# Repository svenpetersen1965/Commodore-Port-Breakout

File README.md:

# Commodore-Port-Breakout
There are five diffenet PCBs.
* 2x12 Breakout: A board that connects to the user port and the IEEE-488 port of the PET
* Cassette Breakout: A board that connects to the Cassette Port of the PET (and C64, C128 and VIC-20)
* Cassette Output: It contains a cassette port board edge connector and connects via a 6p ribbon cable to the Cassette Breakout board.
* IEEE-488 Output: It contains an IEEE-488  port board edge connector and connects via a 26p ribbon cable to the 2x12 Breakout board.
* User Port Output: It contains an User Port port board edge connector and connects via a 26p ribbon cable to the 2x12 Breakout board. It works as well with the C64, C128 and VIC-20

2x12 Breakout:<br>

Cassette Breakout:<br>

Cassette Output:<br>

IEEE-488 Output:<br>

User Port Output:<br>

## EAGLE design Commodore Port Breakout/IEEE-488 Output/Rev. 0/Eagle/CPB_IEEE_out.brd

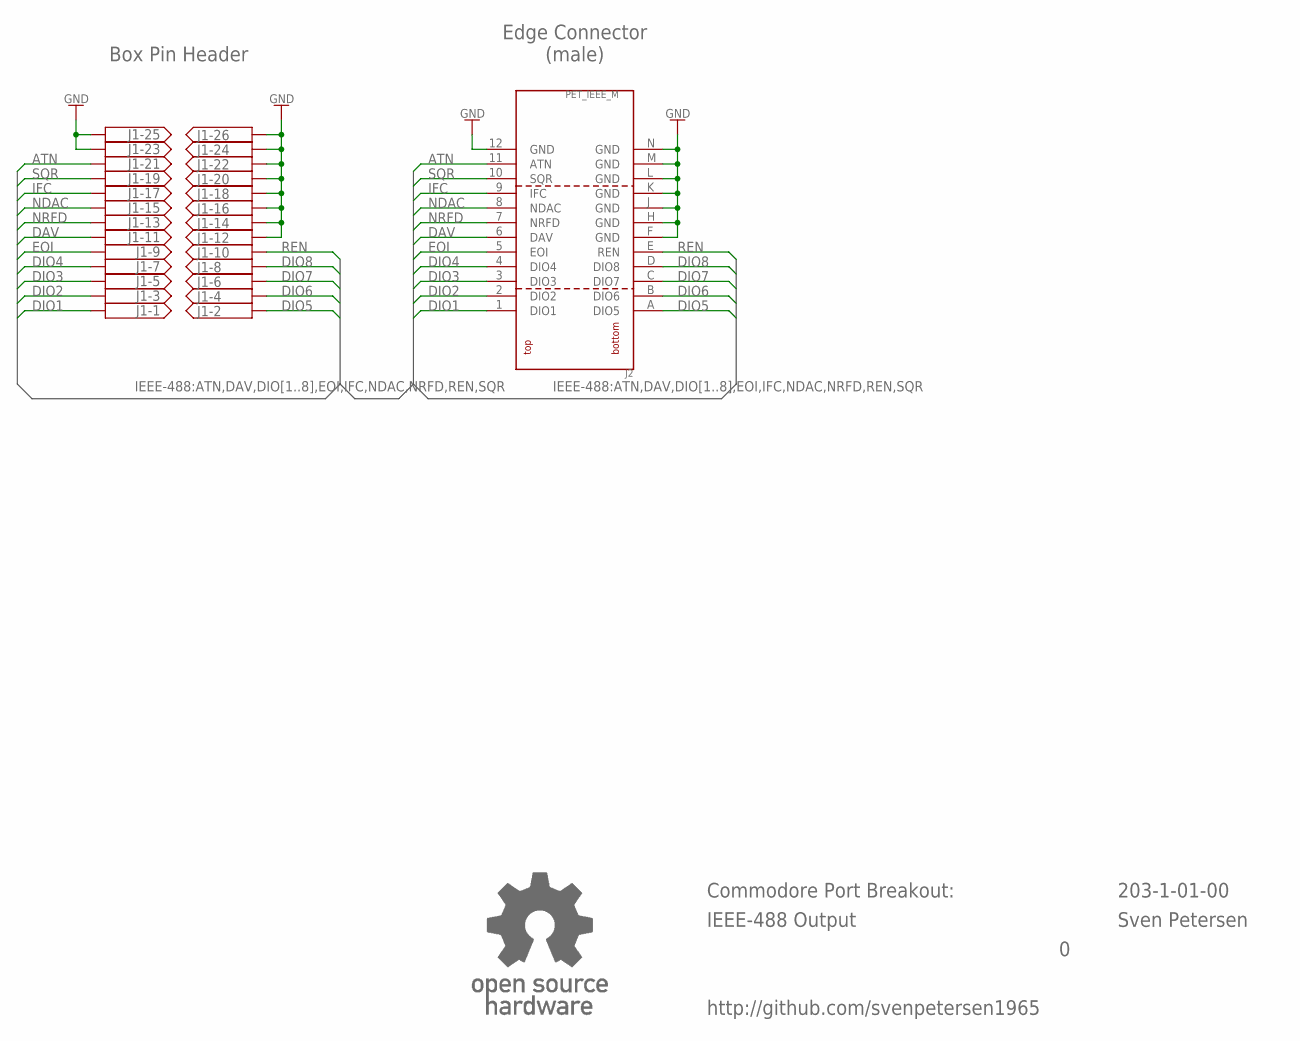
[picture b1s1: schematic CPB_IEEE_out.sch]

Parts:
J1: 2X13WANNE; 2X13WV
J2: PET_IEEE_M
U$9: OPEN_SOURCE_HW; OPENHW

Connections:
ATN: J1.21, J2.11 (ATN)
DAV: J1.11, J2.6 (DAV)
DIO1: J1.1, J2.1 (DIO1)
DIO2: J1.3, J2.2 (DIO2)
DIO3: J1.5, J2.3 (DIO3)
DIO4: J1.7, J2.4 (DIO4)
DIO5: J1.2, J2.A (DIO5)
DIO6: J1.4, J2.B (DIO6)
DIO7: J1.6, J2.C (DIO7)
DIO8: J1.8, J2.D (DIO8)
EOI: J1.9, J2.5 (EOI)
GND: J1.12, J1.14, J1.16, J1.18, J1.20, J1.22, J1.23, J1.24, J1.25, J1.26, J2.12 (GND), J2.F (GND), J2.H (GND), J2.J (GND), J2.K (GND), J2.L (GND), J2.M (GND), J2.N (GND)
IFC: J1.17, J2.9 (IFC)
NDAC: J1.15, J2.8 (NDAC)
NRFD: J1.13, J2.7 (NRFD)
REN: J1.10, J2.E (REN)
SQR: J1.19, J2.10 (SQR)

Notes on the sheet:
Commodore Port Breakout:
203-1-01-00
Sven Petersen
http://github.com/svenpetersen1965
IEEE-488 Output
Edge Connector (male)
Box Pin Header

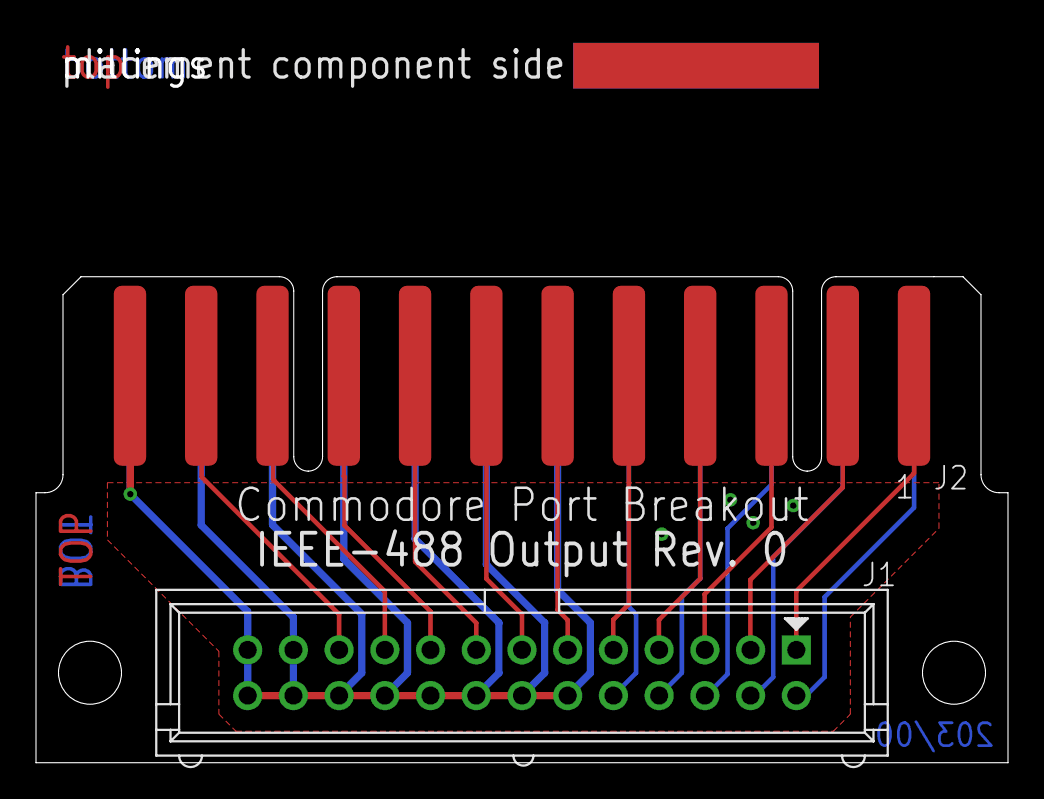
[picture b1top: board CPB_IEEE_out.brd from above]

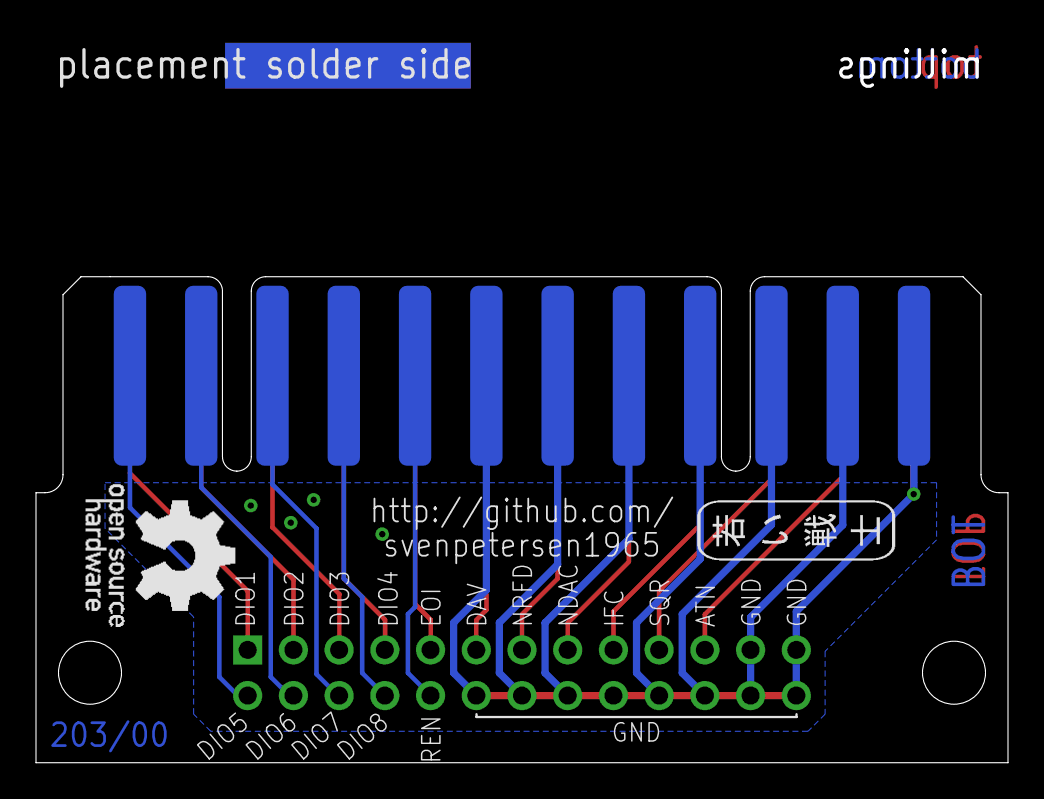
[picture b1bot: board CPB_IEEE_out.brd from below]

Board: 2 copper layers, 54.0 x 40.4 mm, 6 parts (2 on the bottom side), 17 nets.

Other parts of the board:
U$8: PCB-TITLE/
U$10: 2LAYER
U$11: SVEN_TAG

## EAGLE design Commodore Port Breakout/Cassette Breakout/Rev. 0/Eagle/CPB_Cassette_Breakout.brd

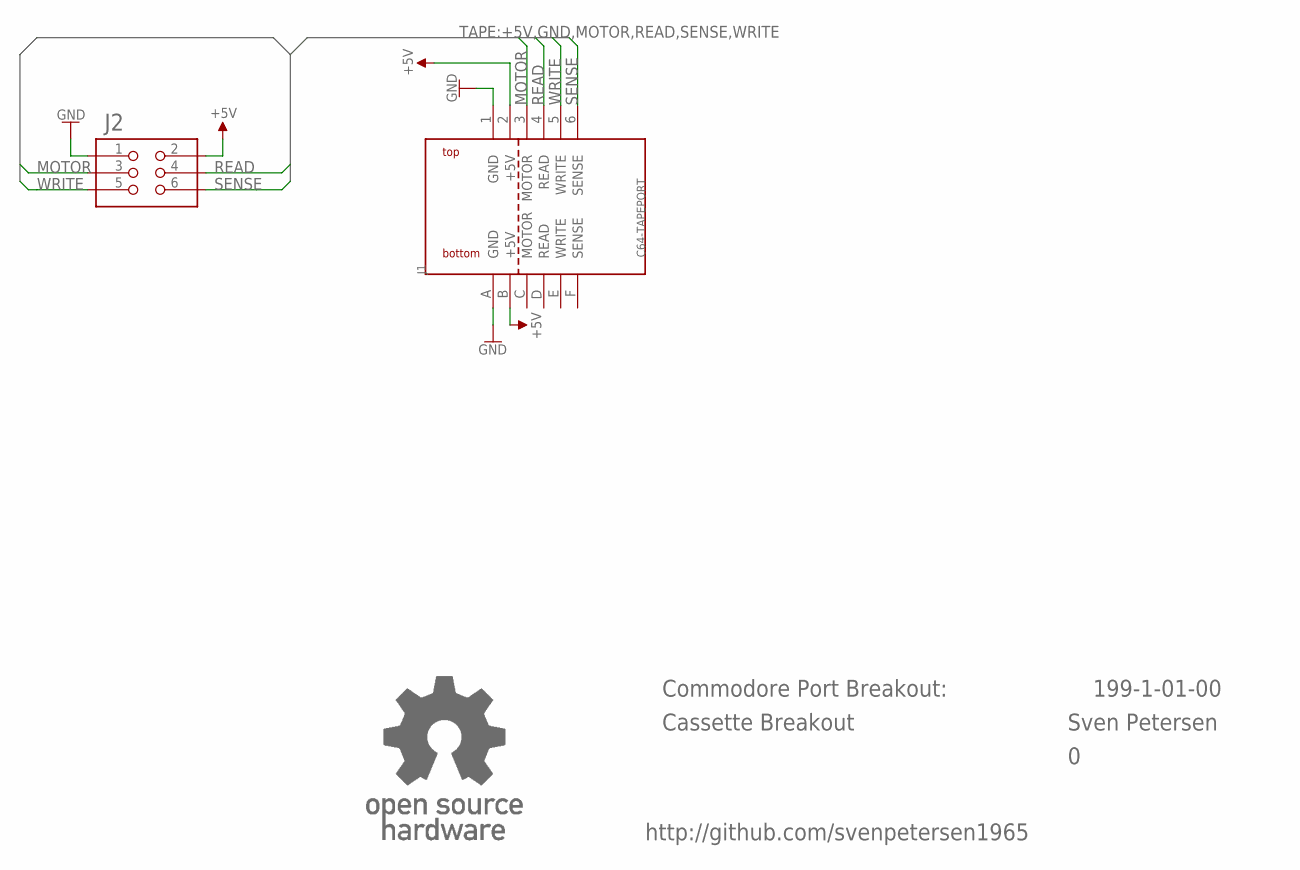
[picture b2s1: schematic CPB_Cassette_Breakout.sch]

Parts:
J1: C64-TAPEPORT; TAPEPORT
J2: 2X03WV
U$18: OPEN_SOURCE_HW; OPENHW

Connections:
+5V: J1.2 (+5V), J1.B (+5V), J2.2
GND: J1.1 (GND), J1.A (GND), J2.1
MOTOR: J1.3 (MOTOR), J2.3
READ: J1.4 (READ), J2.4
SENSE: J1.6 (SENSE), J2.6
WRITE: J1.5 (WRITE), J2.5

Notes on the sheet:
Commodore Port Breakout:
Cassette Breakout
Sven Petersen
199-1-01-00
http://github.com/svenpetersen1965

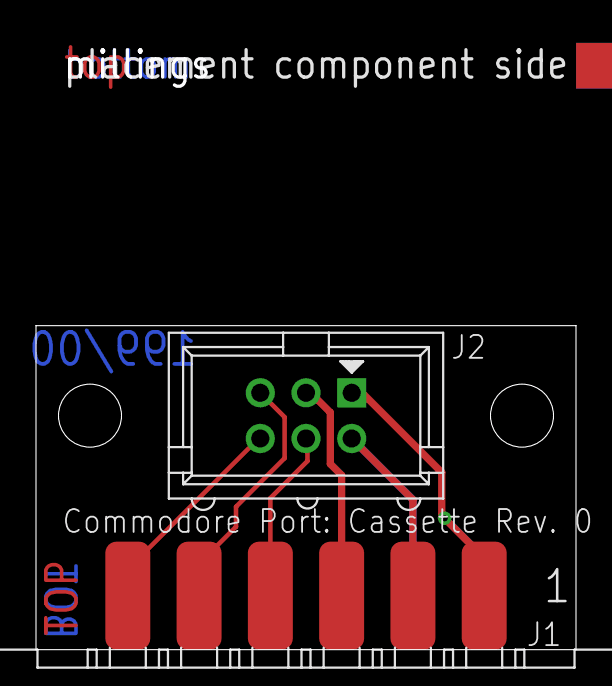
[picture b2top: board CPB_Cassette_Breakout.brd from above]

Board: 2 copper layers, 30.0 x 34.1 mm, 5 parts (1 on the bottom side), 6 nets.

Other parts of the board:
U$5: PCB-TITLE/
U$6: 2LAYER

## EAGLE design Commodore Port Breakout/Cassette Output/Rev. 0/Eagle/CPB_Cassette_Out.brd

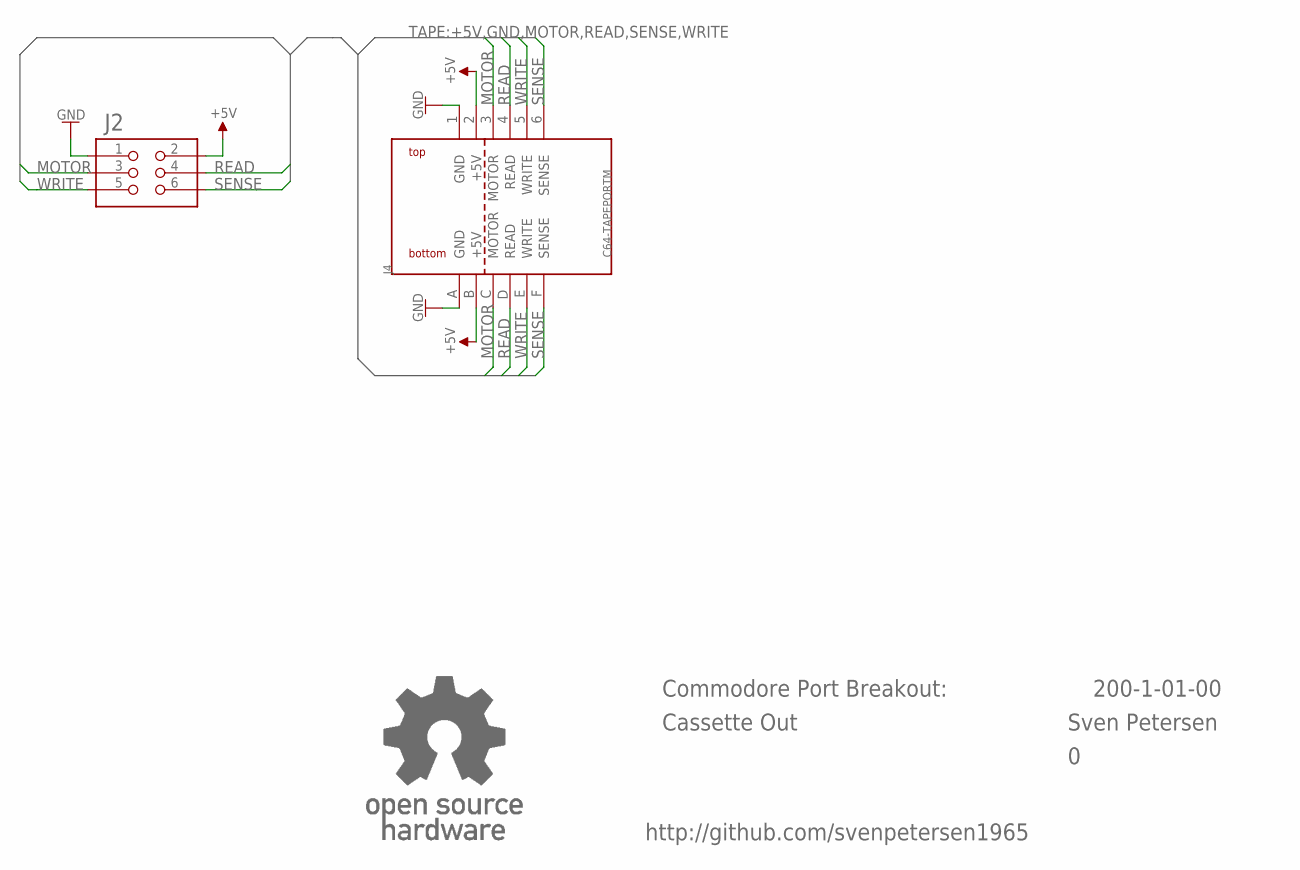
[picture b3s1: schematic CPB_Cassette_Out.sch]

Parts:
J2: 2X03WV
J4: C64-TAPEPORTM; TAPEPORT_M
U$18: OPEN_SOURCE_HW; OPENHW

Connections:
+5V: J2.2, J4.2 (+5V), J4.B (+5V)
GND: J2.1, J4.1 (GND), J4.A (GND)
MOTOR: J2.3, J4.3 (MOTOR), J4.C (MOTOR)
READ: J2.4, J4.4 (READ), J4.D (READ)
SENSE: J2.6, J4.6 (SENSE), J4.F (SENSE)
WRITE: J2.5, J4.5 (WRITE), J4.E (WRITE)

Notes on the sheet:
Commodore Port Breakout:
Cassette Out
Sven Petersen
200-1-01-00
http://github.com/svenpetersen1965

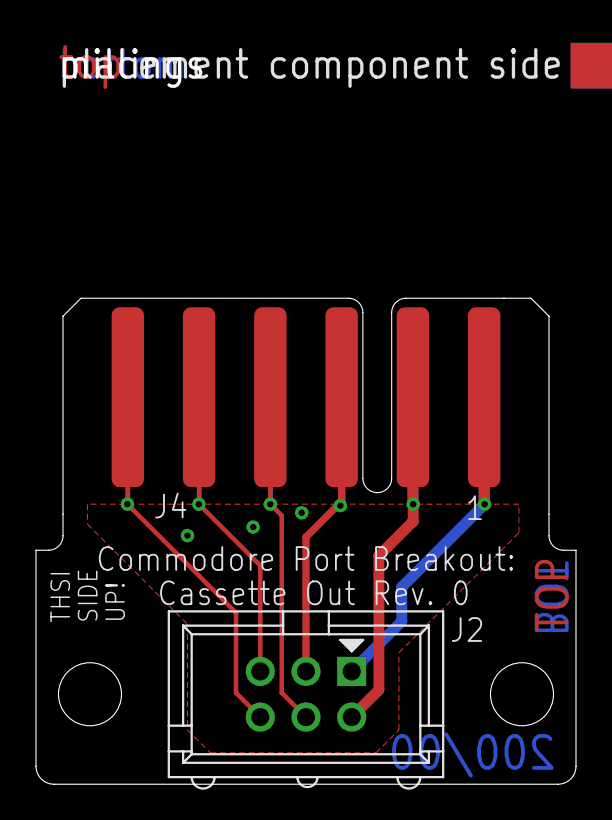
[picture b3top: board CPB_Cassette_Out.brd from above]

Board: 2 copper layers, 30.0 x 41.6 mm, 5 parts (1 on the bottom side), 6 nets.

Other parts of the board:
U$5: PCB-TITLE/
U$6: 2LAYER

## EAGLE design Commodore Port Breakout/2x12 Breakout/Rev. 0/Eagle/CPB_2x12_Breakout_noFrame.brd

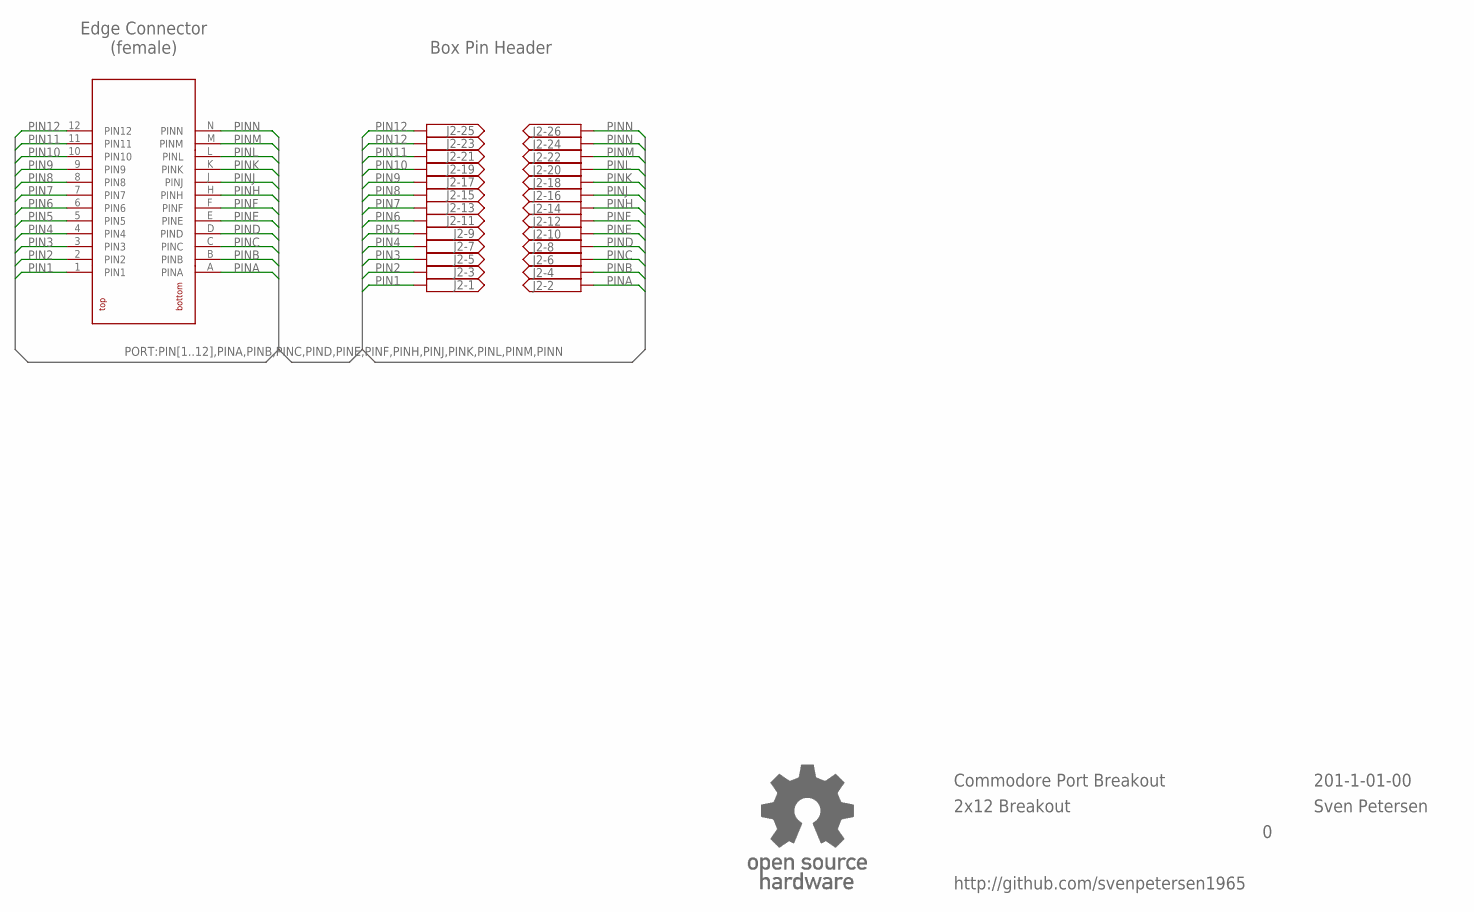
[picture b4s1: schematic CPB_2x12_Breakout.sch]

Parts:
J1: 2X12_PORT
J2: 2X13WANNE; 2X13WV
U$9: OPEN_SOURCE_HW; OPENHW

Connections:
PIN1: J1.1 (PIN1), J2.1
PIN2: J1.2 (PIN2), J2.3
PIN3: J1.3 (PIN3), J2.5
PIN4: J1.4 (PIN4), J2.7
PIN5: J1.5 (PIN5), J2.9
PIN6: J1.6 (PIN6), J2.11
PIN7: J1.7 (PIN7), J2.13
PIN8: J1.8 (PIN8), J2.15
PIN9: J1.9 (PIN9), J2.17
PIN10: J1.10 (PIN10), J2.19
PIN11: J1.11 (PIN11), J2.21
PIN12: J1.12 (PIN12), J2.23, J2.25
PINA: J1.A (PINA), J2.2
PINB: J1.B (PINB), J2.4
PINC: J1.C (PINC), J2.6
PIND: J1.D (PIND), J2.8
PINE: J1.E (PINE), J2.10
PINF: J1.F (PINF), J2.12
PINH: J1.H (PINH), J2.14
PINJ: J1.J (PINJ), J2.16
PINK: J1.K (PINK), J2.18
PINL: J1.L (PINL), J2.20
PINM: J1.M (PINM), J2.22
PINN: J1.N (PINN), J2.24, J2.26

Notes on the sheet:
Commodore Port Breakout
201-1-01-00
Sven Petersen
http://github.com/svenpetersen1965
2x12 Breakout
Edge Connector (female)
Box Pin Header

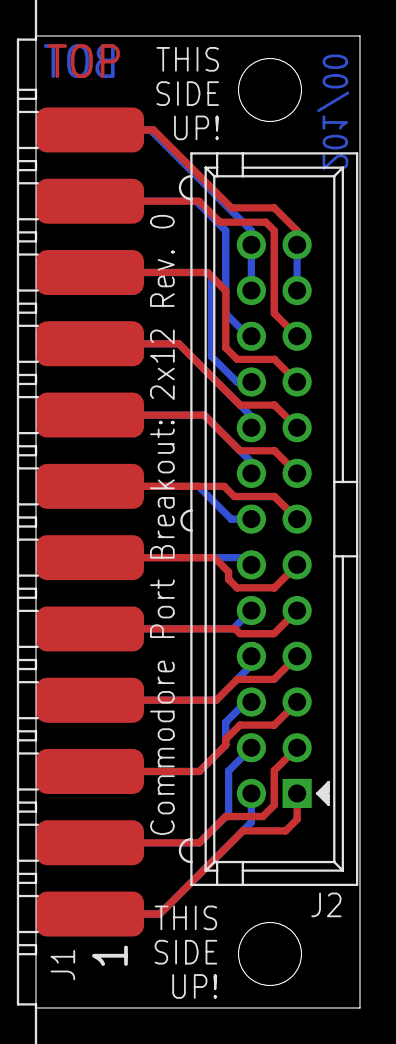
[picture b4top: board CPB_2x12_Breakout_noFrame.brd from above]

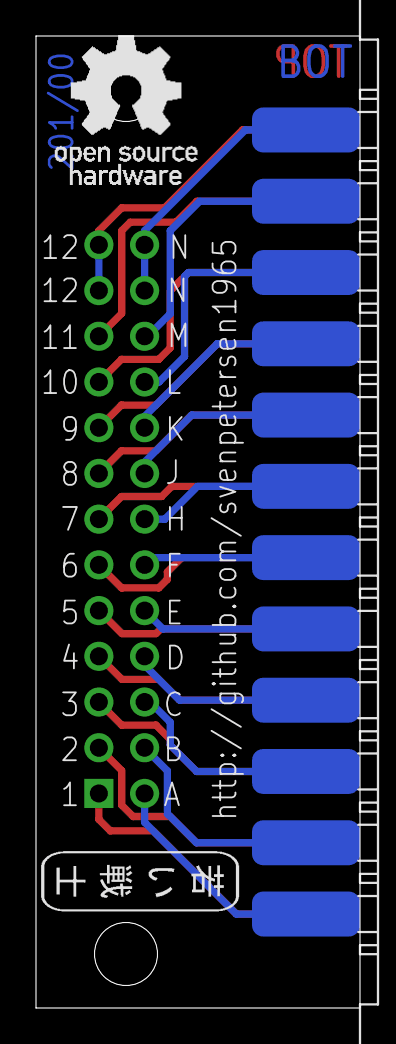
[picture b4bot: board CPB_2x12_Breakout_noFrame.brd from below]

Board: 2 copper layers, 18.0 x 54.0 mm, 5 parts (2 on the bottom side), 24 nets.

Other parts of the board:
U$10: 2LAYER
U$11: SVEN_TAG

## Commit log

2022-11-12 Preliminary release
    This is absolutely preliminary and not tested
2022-11-14 Documentaion added
2022-11-14 Documentation added
2022-11-14 BOM added
2022-11-14 Diocumentation added
2022-11-14 Documenation added
2022-11-14 Create LICENSE
